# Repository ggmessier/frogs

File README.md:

# Fun Frog Project Repository
This repository is for Geoff's various fun projects described in a bit more detail [here](https://lib.engineer/pages/diversions).  Much of my projects are frog themed due to a long time love of [Kermit](https://en.wikipedia.org/wiki/Kermit_the_Frog) and their [role in our ecosystems](https://www.naturewatch.ca/wp-content/biguploads/senior_guide_712.pdf).

## Structure
- `src`: Software source code.
- `boards`: Printed circuit board CAD files.
- `mech`: 3D printer mechanical CAD files.

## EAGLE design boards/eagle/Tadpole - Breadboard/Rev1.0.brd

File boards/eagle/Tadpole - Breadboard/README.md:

# BOM

Digikey part numbers.

| Item       | Number    |  Price | Quantity | 
|:-----------|:---------:|:------:|:--------:|
| Breadboard | 	1738-1321-ND | $4.42 | 1 | 
| JP2 - JP5 Female Header | S7041-ND | $0.93 | 4 |

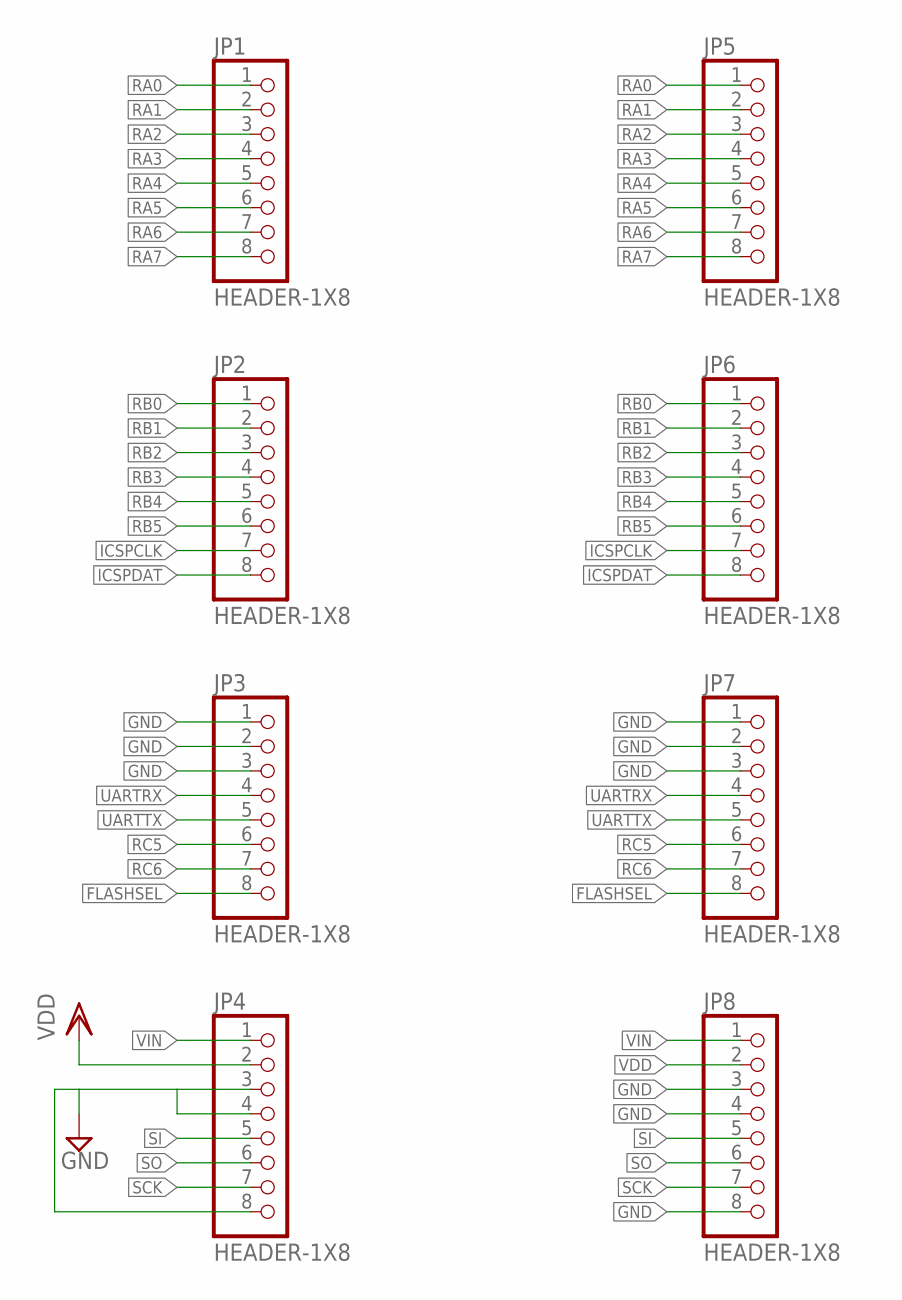
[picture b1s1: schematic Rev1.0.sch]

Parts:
JP1, JP2, JP3, JP4, JP5, JP6, JP7, JP8: HEADER-1X8; 1X08

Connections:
FLASHSEL: JP3.8, JP7.8
GND: JP3.1, JP3.2, JP3.3, JP4.3, JP4.4, JP4.8, JP7.1, JP7.2, JP7.3, JP8.3, JP8.4, JP8.8
ICSPCLK: JP2.7, JP6.7
ICSPDAT: JP2.8, JP6.8
RA0: JP1.1, JP5.1
RA1: JP1.2, JP5.2
RA2: JP1.3, JP5.3
RA3: JP1.4, JP5.4
RA4: JP1.5, JP5.5
RA5: JP1.6, JP5.6
RA6: JP1.7, JP5.7
RA7: JP1.8, JP5.8
RB0: JP2.1, JP6.1
RB1: JP2.2, JP6.2
RB2: JP2.3, JP6.3
RB3: JP2.4, JP6.4
RB4: JP2.5, JP6.5
RB5: JP2.6, JP6.6
RC5: JP3.6, JP7.6
RC6: JP3.7, JP7.7
SCK: JP4.7, JP8.7
SI: JP4.5, JP8.5
SO: JP4.6, JP8.6
UARTRX: JP3.4, JP7.4
UARTTX: JP3.5, JP7.5
VDD: JP4.2, JP8.2
VIN: JP4.1, JP8.1

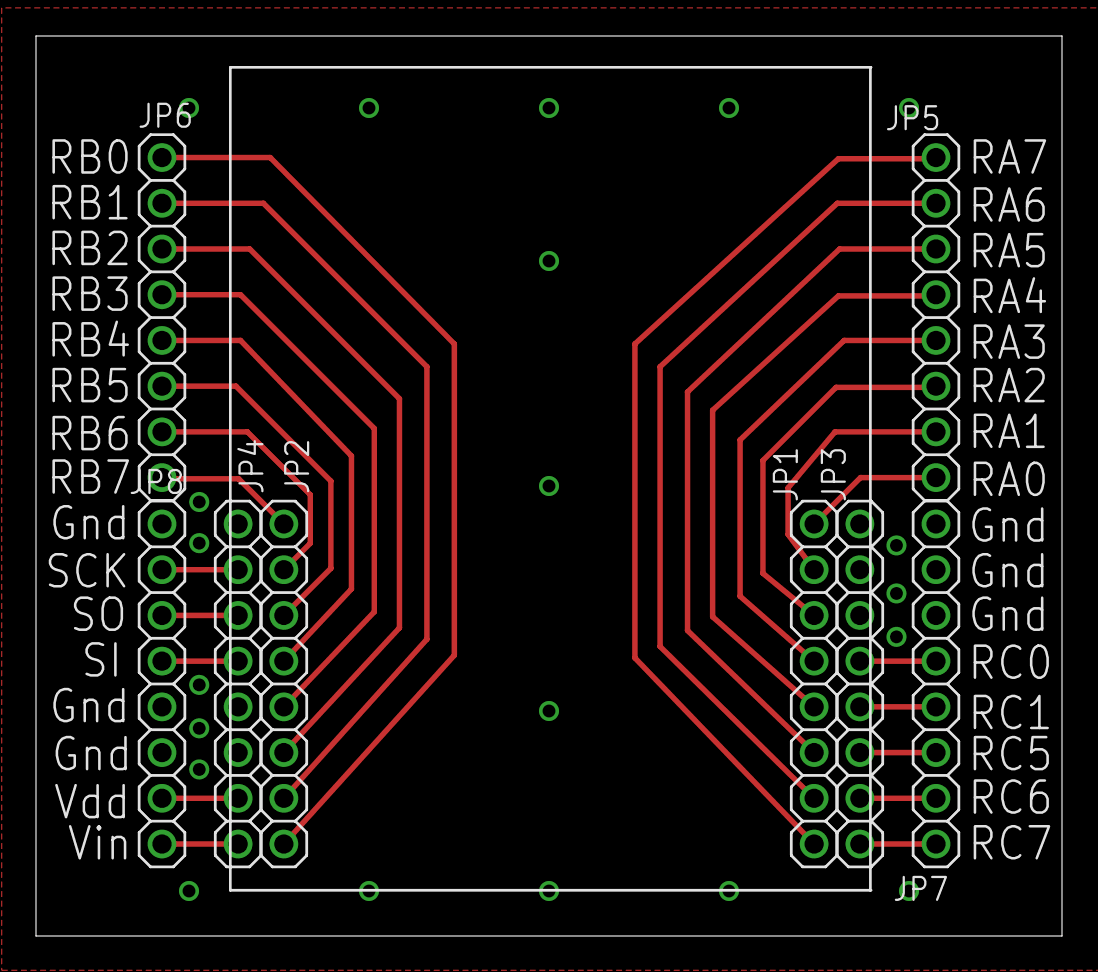
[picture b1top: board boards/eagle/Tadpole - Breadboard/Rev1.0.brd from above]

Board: 2 copper layers, 57.0 x 50.0 mm, 8 parts (0 on the bottom side), 27 nets.

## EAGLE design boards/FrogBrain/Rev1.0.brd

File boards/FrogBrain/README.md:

# BOM

Digikey part numbers.

| Item       | Number    |  Price | Quantity | 
|:-----------|:---------:|:------:|:--------:|
| U1 - 16F1778 PIC     | PIC16F1778-I/SO-ND | $3.35 | 1 |
| U2 - AT25SF321 FLASH | 1265-1279-1-ND | $1.37 | 1 |
| U3 - ADP7104 Regulator | ADP7104ARDZ-3.3-R7CT-ND | $7.34 | 1 |
| SW Reset Switch | CKN9112CT-ND | $0.24 | 1 |
| R1 160~Ohm Resistor | P160DACT-ND | $0.53 | 1 |
| R2 100~kOhm Resistor | P100KDACT-ND | $0.53 | 1 |
| C1,C2 1~uF Capacitor | 311-1365-1-ND | $0.25 | 2 |
| JP2 - JP5 Female Header | S7041-ND | $0.93 | 4 |
| JP1 Right Angle Header | 732-2674-ND | $1.65 | 1 |
| Green LED | 160-1423-1-ND | $0.22 | 1 | 

# Revision History
## Rev 1.1
* Fixed pins 3 and 6 on regulator not connected to ground.

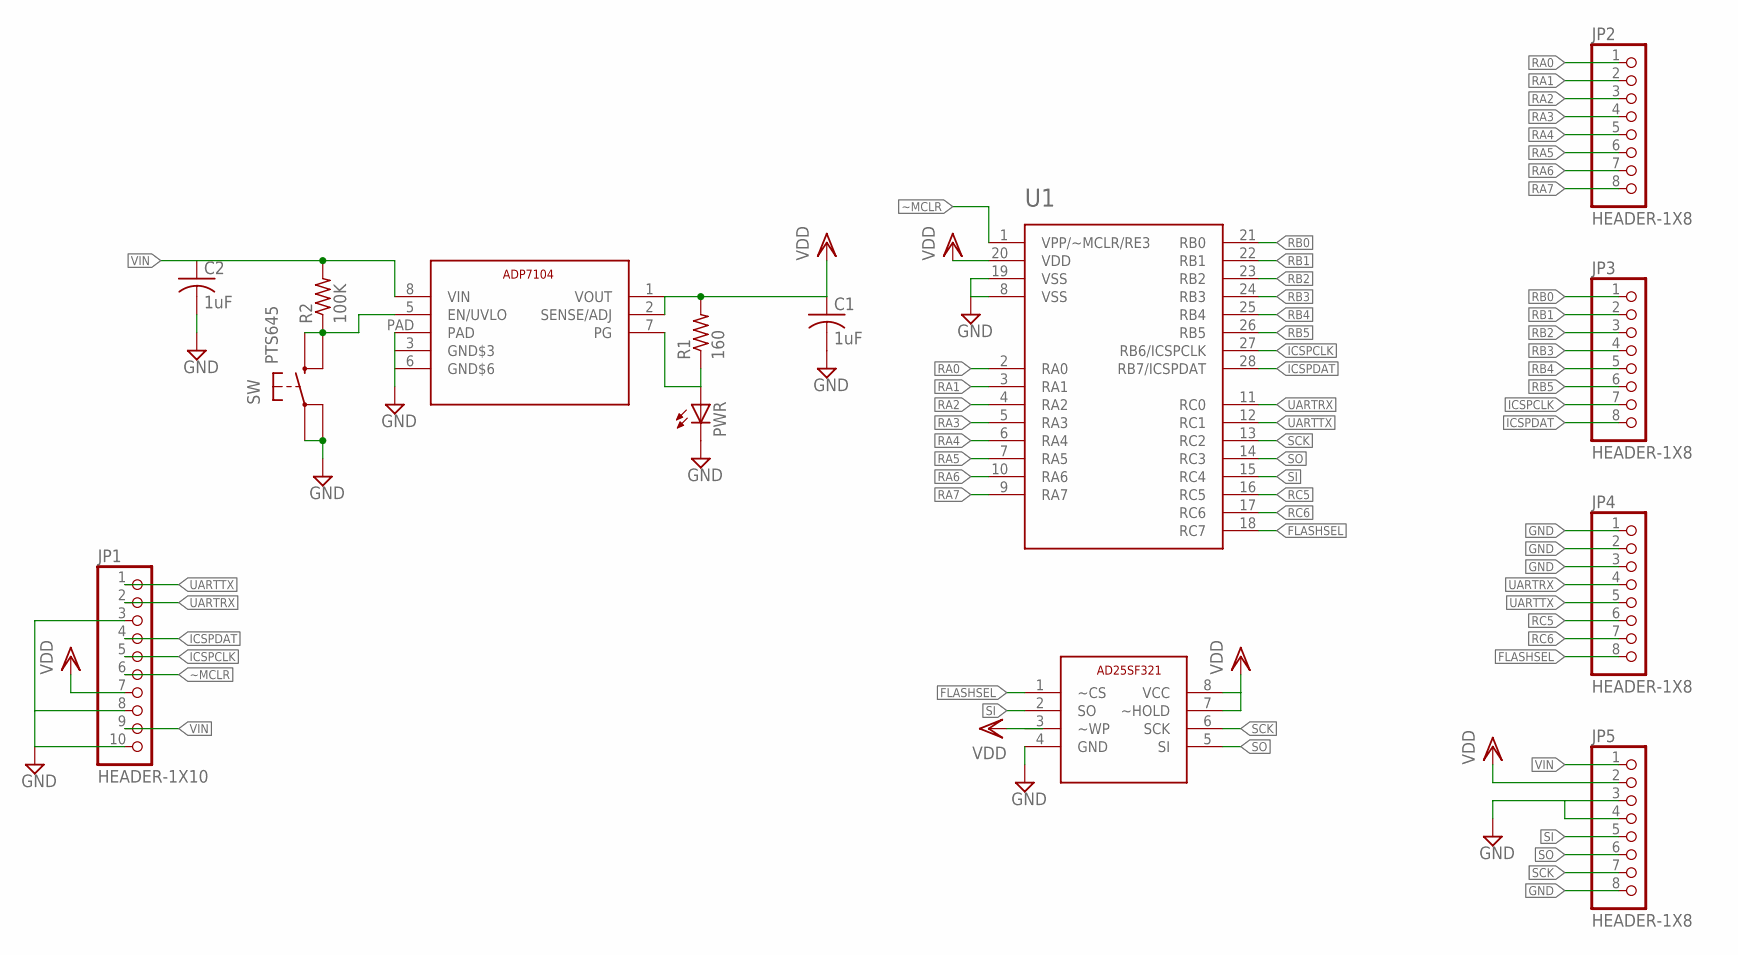
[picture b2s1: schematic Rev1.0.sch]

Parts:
C1, C2: 1uF; C0805
JP1: HEADER-1X10; 1X10
JP2, JP3, JP4, JP5: HEADER-1X8; 1X08
PWR: LEDCHIP-LED0805; CHIP-LED0805
R1: 160; R0805
R2: 100K; R0805
SW: PTS645; TSWITCH-6MM
U1: PIC16F1778; SO28W
U2: AT25SF321; SOIC8
U3: ADP7104; SOIC8-EXP-PAD

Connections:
FLASHSEL: JP4.8, U1.18 (RC7), U2.1 (~CS)
GND: C1.2, C2.2, JP1.3, JP1.8, JP1.10, JP4.1, JP4.2, JP4.3, JP5.3, JP5.4, JP5.8, PWR.C, SW.P$1, SW.P$2, U1.8 (VSS), U1.19 (VSS), U2.4 (GND), U3.PAD
ICSPCLK: JP1.5, JP3.7, U1.27 (RB6/ICSPCLK)
ICSPDAT: JP1.4, JP3.8, U1.28 (RB7/ICSPDAT)
unnamed: PWR.A, R1.1, U3.7 (PG)
unnamed: R2.1, SW.P$3, SW.P$4, U3.5 (EN/UVLO)
RA0: JP2.1, U1.2 (RA0)
RA1: JP2.2, U1.3 (RA1)
RA2: JP2.3, U1.4 (RA2)
RA3: JP2.4, U1.5 (RA3)
RA4: JP2.5, U1.6 (RA4)
RA5: JP2.6, U1.7 (RA5)
RA6: JP2.7, U1.10 (RA6)
RA7: JP2.8, U1.9 (RA7)
RB0: JP3.1, U1.21 (RB0)
RB1: JP3.2, U1.22 (RB1)
RB2: JP3.3, U1.23 (RB2)
RB3: JP3.4, U1.24 (RB3)
RB4: JP3.5, U1.25 (RB4)
RB5: JP3.6, U1.26 (RB5)
RC5: JP4.6, U1.16 (RC5)
RC6: JP4.7, U1.17 (RC6)
SCK: JP5.7, U1.13 (RC2), U2.6 (SCK)
SI: JP5.5, U1.15 (RC4), U2.2 (SO)
SO: JP5.6, U1.14 (RC3), U2.5 (SI)
UARTRX: JP1.2, JP4.4, U1.11 (RC0)
UARTTX: JP1.1, JP4.5, U1.12 (RC1)
VDD: C1.1, JP1.7, JP5.2, R1.2, U1.20 (VDD), U2.7 (~HOLD), U2.8 (VCC), U3.1 (VOUT), U3.2 (SENSE/ADJ)
VIN: C2.1, JP1.9, JP5.1, R2.2, U3.8 (VIN)
~MCLR: JP1.6, U1.1 (VPP/~MCLR/RE3)

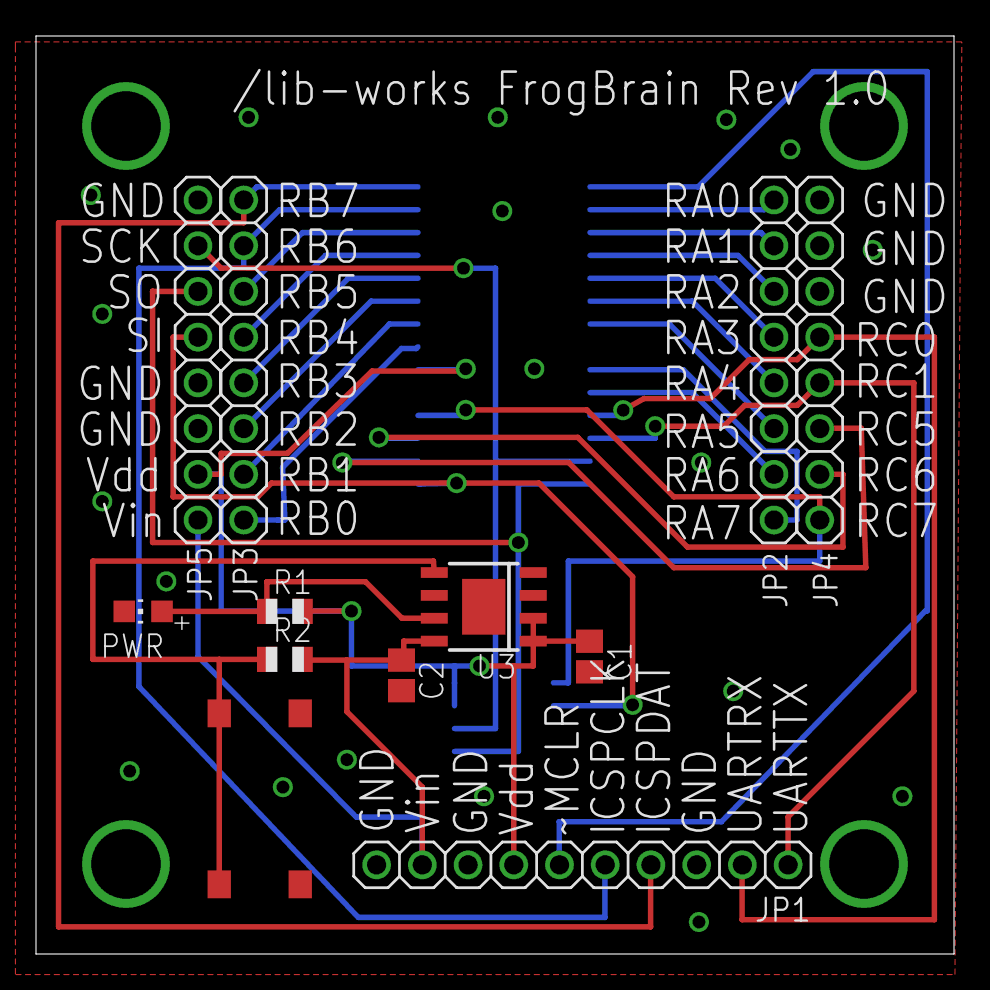
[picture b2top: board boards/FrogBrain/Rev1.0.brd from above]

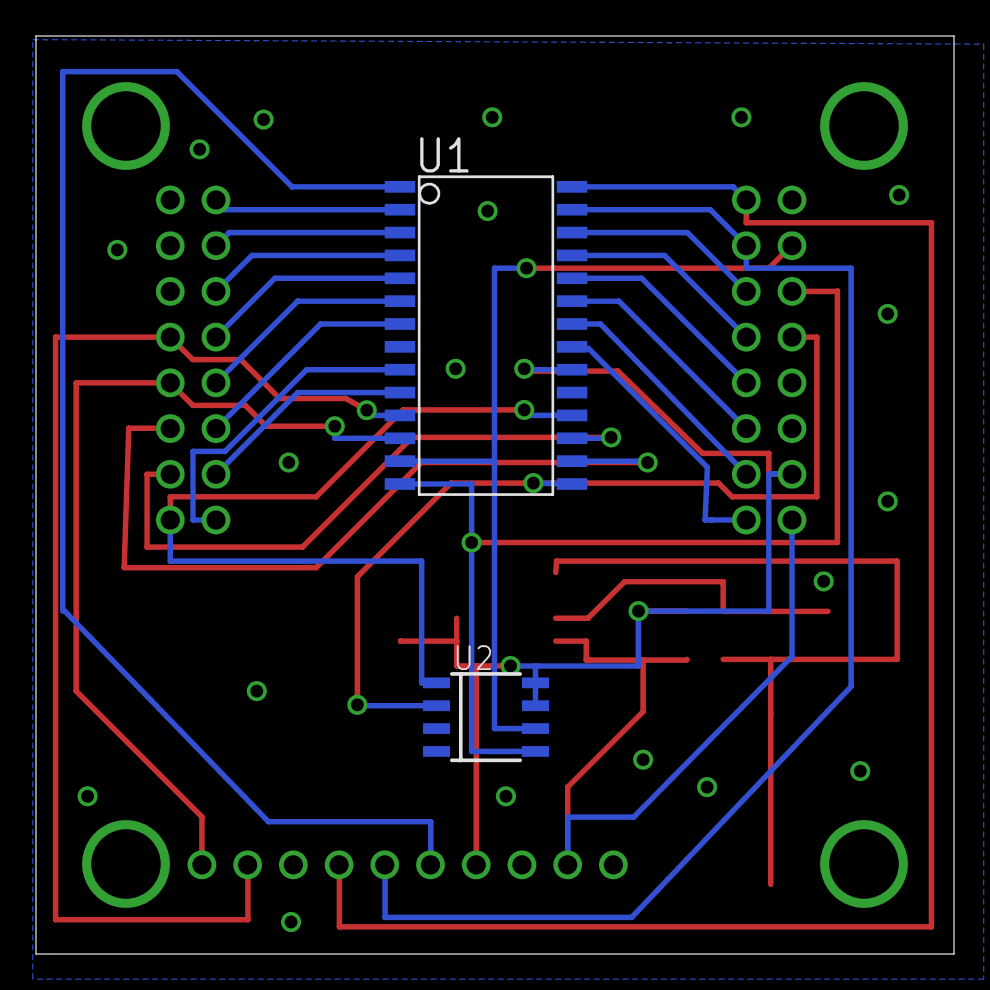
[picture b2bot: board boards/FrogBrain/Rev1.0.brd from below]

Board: 2 copper layers, 51.0 x 51.0 mm, 14 parts (2 on the bottom side), 30 nets.

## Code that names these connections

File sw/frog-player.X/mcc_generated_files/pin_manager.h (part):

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// get/set IO_RA0 aliases
#define IO_RA0_TRIS                 TRISAbits.TRISA0
#define IO_RA0_LAT                  LATAbits.LATA0
#define IO_RA0_PORT                 PORTAbits.RA0
#define IO_RA0_WPU                  WPUAbits.WPUA0
#define IO_RA0_OD                   ODCONAbits.ODA0
#define IO_RA0_ANS                  ANSELAbits.ANSA0
#define IO_RA0_SetHigh()            do { LATAbits.LATA0 = 1; } while(0)
#define IO_RA0_SetLow()             do { LATAbits.LATA0 = 0; } while(0)
#define IO_RA0_Toggle()             do { LATAbits.LATA0 = ~LATAbits.LATA0; } while(0)
#define IO_RA0_GetValue()           PORTAbits.RA0
#define IO_RA0_SetDigitalInput()    do { TRISAbits.TRISA0 = 1; } while(0)
#define IO_RA0_SetDigitalOutput()   do { TRISAbits.TRISA0 = 0; } while(0)
#define IO_RA0_SetPullup()          do { WPUAbits.WPUA0 = 1; } while(0)
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#define RA1_SetHigh()               do { LATAbits.LATA1 = 1; } while(0)
#define RA1_SetLow()                do { LATAbits.LATA1 = 0; } while(0)
#define RA1_Toggle()                do { LATAbits.LATA1 = ~LATAbits.LATA1; } while(0)
#define RA1_GetValue()              PORTAbits.RA1
#define RA1_SetDigitalInput()       do { TRISAbits.TRISA1 = 1; } while(0)
#define RA1_SetDigitalOutput()      do { TRISAbits.TRISA1 = 0; } while(0)
#define RA1_SetPullup()             do { WPUAbits.WPUA1 = 1; } while(0)
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#define RA2_SetHigh()               do { LATAbits.LATA2 = 1; } while(0)
#define RA2_SetLow()                do { LATAbits.LATA2 = 0; } while(0)
#define RA2_Toggle()                do { LATAbits.LATA2 = ~LATAbits.LATA2; } while(0)
#define RA2_GetValue()              PORTAbits.RA2
#define RA2_SetDigitalInput()       do { TRISAbits.TRISA2 = 1; } while(0)
#define RA2_SetDigitalOutput()      do { TRISAbits.TRISA2 = 0; } while(0)
#define RA2_SetPullup()             do { WPUAbits.WPUA2 = 1; } while(0)
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#define RA5_SetHigh()               do { LATAbits.LATA5 = 1; } while(0)
#define RA5_SetLow()                do { LATAbits.LATA5 = 0; } while(0)
#define RA5_Toggle()                do { LATAbits.LATA5 = ~LATAbits.LATA5; } while(0)
#define RA5_GetValue()              PORTAbits.RA5
#define RA5_SetDigitalInput()       do { TRISAbits.TRISA5 = 1; } while(0)
#define RA5_SetDigitalOutput()      do { TRISAbits.TRISA5 = 0; } while(0)
#define RA5_SetPullup()             do { WPUAbits.WPUA5 = 1; } while(0)
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#define RC0_SetHigh()               do { LATCbits.LATC0 = 1; } while(0)
#define RC0_SetLow()                do { LATCbits.LATC0 = 0; } while(0)
#define RC0_Toggle()                do { LATCbits.LATC0 = ~LATCbits.LATC0; } while(0)
#define RC0_GetValue()              PORTCbits.RC0
#define RC0_SetDigitalInput()       do { TRISCbits.TRISC0 = 1; } while(0)
#define RC0_SetDigitalOutput()      do { TRISCbits.TRISC0 = 0; } while(0)
#define RC0_SetPullup()             do { WPUCbits.WPUC0 = 1; } while(0)
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#define RC1_SetHigh()               do { LATCbits.LATC1 = 1; } while(0)
#define RC1_SetLow()                do { LATCbits.LATC1 = 0; } while(0)
#define RC1_Toggle()                do { LATCbits.LATC1 = ~LATCbits.LATC1; } while(0)
#define RC1_GetValue()              PORTCbits.RC1
#define RC1_SetDigitalInput()       do { TRISCbits.TRISC1 = 1; } while(0)
#define RC1_SetDigitalOutput()      do { TRISCbits.TRISC1 = 0; } while(0)
#define RC1_SetPullup()             do { WPUCbits.WPUC1 = 1; } while(0)
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// get/set SCK aliases
#define SCK_TRIS                 TRISCbits.TRISC2
#define SCK_LAT                  LATCbits.LATC2
#define SCK_PORT                 PORTCbits.RC2
#define SCK_WPU                  WPUCbits.WPUC2
#define SCK_OD                   ODCONCbits.ODC2
#define SCK_ANS                  ANSELCbits.ANSC2
#define SCK_SetHigh()            do { LATCbits.LATC2 = 1; } while(0)
#define SCK_SetLow()             do { LATCbits.LATC2 = 0; } while(0)
#define SCK_Toggle()             do { LATCbits.LATC2 = ~LATCbits.LATC2; } while(0)
#define SCK_GetValue()           PORTCbits.RC2
#define SCK_SetDigitalInput()    do { TRISCbits.TRISC2 = 1; } while(0)
#define SCK_SetDigitalOutput()   do { TRISCbits.TRISC2 = 0; } while(0)
#define SCK_SetPullup()          do { WPUCbits.WPUC2 = 1; } while(0)
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// get/set SDO aliases
#define SDO_TRIS                 TRISCbits.TRISC3
#define SDO_LAT                  LATCbits.LATC3
#define SDO_PORT                 PORTCbits.RC3
#define SDO_WPU                  WPUCbits.WPUC3
#define SDO_OD                   ODCONCbits.ODC3
#define SDO_ANS                  ANSELCbits.ANSC3
#define SDO_SetHigh()            do { LATCbits.LATC3 = 1; } while(0)
#define SDO_SetLow()             do { LATCbits.LATC3 = 0; } while(0)
#define SDO_Toggle()             do { LATCbits.LATC3 = ~LATCbits.LATC3; } while(0)
#define SDO_GetValue()           PORTCbits.RC3
#define SDO_SetDigitalInput()    do { TRISCbits.TRISC3 = 1; } while(0)
#define SDO_SetDigitalOutput()   do { TRISCbits.TRISC3 = 0; } while(0)
#define SDO_SetPullup()          do { WPUCbits.WPUC3 = 1; } while(0)
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// get/set SDI aliases
#define SDI_TRIS                 TRISCbits.TRISC4
#define SDI_LAT                  LATCbits.LATC4
#define SDI_PORT                 PORTCbits.RC4
#define SDI_WPU                  WPUCbits.WPUC4
#define SDI_OD                   ODCONCbits.ODC4
#define SDI_ANS                  ANSELCbits.ANSC4
#define SDI_SetHigh()            do { LATCbits.LATC4 = 1; } while(0)
#define SDI_SetLow()             do { LATCbits.LATC4 = 0; } while(0)
#define SDI_Toggle()             do { LATCbits.LATC4 = ~LATCbits.LATC4; } while(0)
#define SDI_GetValue()           PORTCbits.RC4
#define SDI_SetDigitalInput()    do { TRISCbits.TRISC4 = 1; } while(0)
#define SDI_SetDigitalOutput()   do { TRISCbits.TRISC4 = 0; } while(0)
#define SDI_SetPullup()          do { WPUCbits.WPUC4 = 1; } while(0)
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// get/set IO_RC7 aliases
#define IO_RC7_TRIS                 TRISCbits.TRISC7
#define IO_RC7_LAT                  LATCbits.LATC7
#define IO_RC7_PORT                 PORTCbits.RC7
#define IO_RC7_WPU                  WPUCbits.WPUC7
#define IO_RC7_OD                   ODCONCbits.ODC7
#define IO_RC7_ANS                  ANSELCbits.ANSC7
#define IO_RC7_SetHigh()            do { LATCbits.LATC7 = 1; } while(0)
#define IO_RC7_SetLow()             do { LATCbits.LATC7 = 0; } while(0)
#define IO_RC7_Toggle()             do { LATCbits.LATC7 = ~LATCbits.LATC7; } while(0)
#define IO_RC7_GetValue()           PORTCbits.RC7
#define IO_RC7_SetDigitalInput()    do { TRISCbits.TRISC7 = 1; } while(0)
#define IO_RC7_SetDigitalOutput()   do { TRISCbits.TRISC7 = 0; } while(0)
#define IO_RC7_SetPullup()          do { WPUCbits.WPUC7 = 1; } while(0)
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
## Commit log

2018-05-18 Init dir structure and Rev 1.0 of FrogBrain.
2018-05-31 Final rev 1.0 brain and initial tadpole breadboard.
2018-05-31 Fixing README tables.
2018-05-31 Error in tadpole BOM.
2018-07-27 Added rev1.1 of the frog brain.
2018-08-20 Kermit PIC protocol and small frogbrain board mods.
2019-05-06 Post ILS code modifications (needs cleaning).
2019-05-06 Added GUI directory and modified ILS player files.
2020-05-26 Gandalf sync. 3D print additions.
2020-06-22 File clean-up and GUI repository merge.
2020-06-22 Updated GUI README.
2020-08-04 BBB GPIO code, makey head and dir reorg.
2022-12-11 Re-organization (long overdue push).
2022-12-22 dAuratus board development begins. AVR code cleanup.
2022-12-28 AVR UART menu code and AVR library framework added.
2023-04-07 Version 1.0 of fan control software.
2023-07-16 Soil moisture spice simulation. Some AVR code mods.
2024-01-14 Huge update, long overdue.
2024-11-30 Long overdue update: PCB directory cleanup, ILS board modifications, misc household 3D print projects, AVR code for fan control and temperature sensing.

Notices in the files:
sw/frog-player.X/mcc_generated_files/pin_manager.h:
(c) 2018 Microchip Technology Inc. and its subsidiaries.
